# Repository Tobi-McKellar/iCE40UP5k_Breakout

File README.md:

This is a simple FPGA breakout board based on the iCE40UP5K. Exposing 16 GPIO via two 6x1 PMOD ports and one 6x2 PMOD port, as well as 11 LEDs, 3 buttons, and one capacitive touch button, the board can be powered via USB-C or the appropriate mounting holes. Programmed via [SOIC-Bite](https://github.com/SimonMerrett/SOICbite/blob/master/README.md). The schematic and PCB can be viewed online [here](https://kicanvas.org/?github=https%3A%2F%2Fgithub.com%2FTobi-McKellar%2FiCE40UP5k_Breakout%2Ftree%2Fmain%2FFPGA_SOM) via KiCanvas.

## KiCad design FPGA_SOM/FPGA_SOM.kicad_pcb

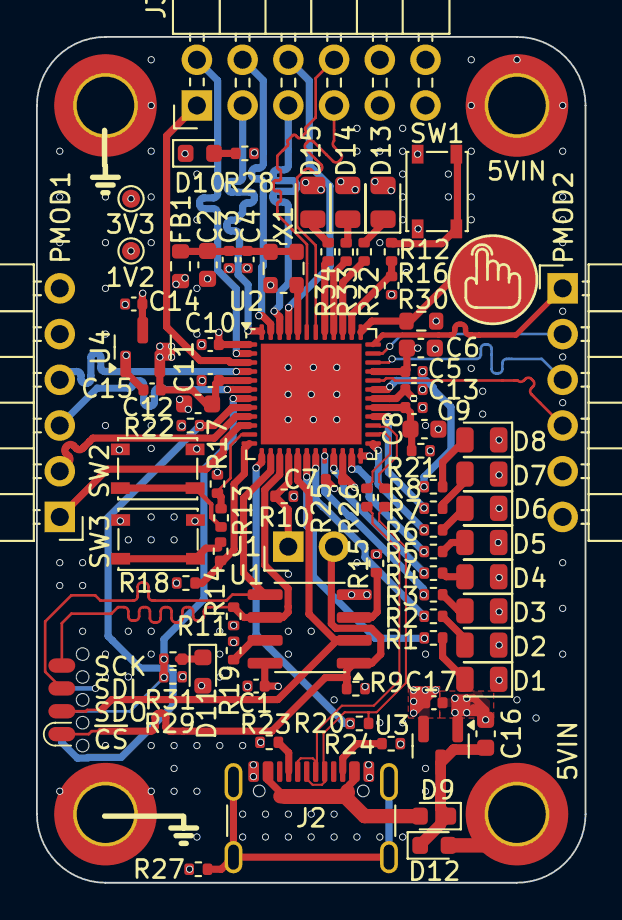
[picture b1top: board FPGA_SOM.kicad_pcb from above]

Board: 6 copper layers, 30.5 x 47.0 mm, 88 parts (0 on the bottom side), 73 nets.

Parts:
C1, C3, C5, C7, C9, C10, C11, C13: 100n; C_0402_1005Metric
C2, C16: 10u; C_0603_1608Metric
C4: 10n; C_0402_1005Metric
C6, C8, C12: 4.7u; C_0603_1608Metric
C14, C15, C17: 1u; C_0402_1005Metric
D1, D2, D14: GLED; LED_0805_2012Metric
D3, D4, D15: BLED; LED_0805_2012Metric
D5, D6: YLED; LED_0805_2012Metric
D7, D8, D13: RLED; LED_0805_2012Metric
D9, D12: D_Schottky; D_0603_1608Metric
D10, D11: LED; D_0603_1608Metric
FB1: FerriteBead; R_0603_1608Metric
H1, H2, H3, H4: MountingHole_Pad; MountingHole_3.2mm_M3_ISO7380_Pad_TopBottom
J1: Conn_01x02; PinHeader_1x02_P2.54mm_Vertical
J2: USB_C_Receptacle_USB2.0; USB_C_Receptacle_GCT_USB4105-xx-A_16P_TopMnt_Horizontal
J3: Conn_02x06_Top_Bottom; PinHeader_2x06_P2.54mm_Horizontal
J4: Conn_02x04_Counter_Clockwise; SOIC_clipProgSmall
J5, J6: Conn_01x06; PinHeader_1x06_P2.54mm_Horizontal
R1, R2, R3, R4, R5, R6: 470; R_0402_1005Metric
R7, R8, R12, R13, R14: 1k; R_0402_1005Metric
R9, R10, R11, R15, R16, R17, R18, R19, R22: 10k; R_0402_1005Metric
R20: 1k5; R_0402_1005Metric
R21: 100; R_0402_1005Metric
R23, R24: 5k1; R_0402_1005Metric
R25, R26: 22; R_0402_1005Metric
R27: 0; R_0402_1005Metric
R28, R31, R32, R33, R34: 2k2; R_0402_1005Metric
R29: 4k7; R_0402_1005Metric
R30: 1M; R_0603_1608Metric
SW1, SW2, SW3: SW_Push; SW_SPST_PTS810
TP1: 3V3; TestPoint_Pad_D1.0mm
TP2: 1V2; TestPoint_Pad_D1.0mm
U1: W25Q128JVSIQ; SOIC-8_3.9x4.9mm_P1.27mm
U2: ICE40UP5K-SG48ITR; QFN-48-1EP_7x7mm_P0.5mm_EP5.6x5.6mm
U3: AP2127N-3.3; SOT-23
U4: AP2127N-1.2; SOT-23
U5: Capacitive_touchpad
X1: SX2M36.000B10F20TNN; Oscillator_SMD_ECS_2520MV-xxx-xx-4Pin_2.5x2.0mm

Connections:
+5V: C16.2, D9.1 (K), D12.1 (K), U3.3 (VI)
/1V2: C11.1, C12.1, C13.1, C15.1, R21.2, TP2.1, U2.5 (VCC), U2.30 (VCC), U4.2 (VO)
/3V3: C1.1, C5.1, C6.1, C7.1, C10.1, C14.2, C17.1, D11.2 (A), D13.2 (A), D14.2 (A), D15.2 (A), FB1.1, J3.11, J3.12, J5.6, J6.6, R9.1, R10.1, R11.1, R15.1, R19.1, R22.1, R28.1, R29.1, R30.1, SW1.1, SW2.1, SW3.1, TP1.1, U1.8 (VCC), U2.1 (VCCIO_2), U2.22 (SPI_VCCIO1), U2.24 (VPP_2V5), U2.33 (VCCIO_0), U3.2 (VO), U4.3 (VI)
/31_button: R12.1, R16.2, U2.38 (IOT_50b)
/BLED0: R3.2, U2.20 (IOB_25b_G3)
/BLED1: R4.2, U2.21 (IOB_23b)
/Button_2: R13.1, R17.2, U2.11 (IOB_20a)
/Button_6: R14.1, R18.2, U2.12 (IOB_22a)
/CDONE: J4.7, R29.2, R31.1, U2.7 (CDONE)
/CLK_IN_G6: U2.44 (IOB_3b_G6), X1.3 (OUT)
/CRESET: J4.8, R22.2, U2.8 (~CRESET)
/Cap_touch: R30.2, U2.37 (IOT_45a_G1), U5.1 (Sense)
/D_N: R25.2, U2.26 (IOT_39a)
/D_P: R26.2, U2.27 (IOT_38b)
/Din_N: J2.A7 (D-), J2.B7 (D-), R25.1
/Din_P: J2.A6 (D+), J2.B6 (D+), R20.1, R26.1
/FLASH_DI: J4.3, U1.5 (DI(IO0)), U2.14 (IOB_32a_SPI_SO)
/FLASH_DO: J4.2, U1.2 (DO(IO1)), U2.17 (IOB_33b_SPI_SI)
/FLASH_SS: J1.2, J4.1, R9.2, U1.1 (~CS)
/GLED0: R1.2, U2.18 (IOB_31b)
/GLED1: R2.2, U2.19 (IOB_29b)
/ICE_SS: J1.1, R10.2, U2.16 (IOB_35b_SPI_SS)
/PMOD1_25: J5.4, U2.4 (IOB_8a)
/PMOD1_26: J5.2, U2.9 (IOB_16a)
/PMOD1_27: J5.3, U2.6 (IOB_13b)
/PMOD1_28: J5.1, U2.10 (IOB_18a)
/PMOD2_45: J3.4, U2.47 (IOB_2a)
/PMOD2_46: J3.3, U2.48 (IOB_4a)
/PMOD2_47: J3.2, U2.2 (IOB_6a)
/PMOD2_48: J3.1, U2.3 (IOB_9b)
/PMOD3_32: J6.4, U2.32 (IOT_43a)
/PMOD3_34: J6.3, U2.34 (IOT_44b)
/PMOD3_35_G0: J6.2, U2.35 (IOT_46b_G0)
/PMOD3_36: J6.1, U2.36 (IOT_48b)
/PMOD3_37_G1: J3.8, U2.43 (IOT_49a)
/PMOD3_38: J3.7, U2.42 (IOT_51a)
/PMOD3_42: J3.6, U2.45 (IOB_5b)
/PMOD3_43: J3.5, U2.46 (IOB_0a)
/RGB0: R32.1, U2.39 (RGB0)
/RGB1: R33.1, U2.40 (RGB1)
/RGB2: R34.1, U2.41 (RGB2)
/RLED0: R7.2, U2.28 (IOT_41a)
/RLED1: R8.2, U2.31 (IOT_42b)
/SCK: J4.4, R11.2, U1.6 (SCK), U2.15 (IOB_34a_SPI_SCK)
/USB_Detect: R20.2, U2.13 (IOB_24a)
/VCCPLL: C8.1, C9.1, R21.1, U2.29 (VCCPLL)
/V_OSC: C2.1, C3.1, C4.2, FB1.2, X1.1 (Tri-State), X1.4 (VDD)
/YLED0: R5.2, U2.23 (IOT_37a)
/YLED1: R6.2, U2.25 (IOT_36b)
GND: C1.2, C2.2, C3.2, C4.1, C5.2, C6.2, C7.2, C8.2, C9.2, C10.2, C11.2, C12.2, C13.2, C14.1, C15.2, C16.1, C17.2, D1.1 (K), D2.1 (K), D3.1 (K), D4.1 (K), D5.1 (K), D6.1 (K), D7.1 (K), D8.1 (K), D10.1 (K), H3.1, H4.1, J2.A1 (GND), J2.A12 (GND), J2.B1 (GND), J2.B12 (GND), J3.9, J3.10, J4.6, J5.5, J6.5, R16.1, R17.1, R18.1, R23.2, R24.2, R27.2, U1.4 (GND), U2.49 (GND), U3.1 (GND), U4.1 (GND), X1.2 (GND)
unnamed: D1.2 (A), R1.1
unnamed: D2.2 (A), R2.1
unnamed: D3.2 (A), R3.1
unnamed: D4.2 (A), R4.1
unnamed: D5.2 (A), R5.1
unnamed: D6.2 (A), R6.1
unnamed: D7.2 (A), R7.1
unnamed: D8.2 (A), R8.1
unnamed: D9.2 (A), J2.A4 (VBUS), J2.A9 (VBUS), J2.B4 (VBUS), J2.B9 (VBUS)
unnamed: D10.2 (A), R28.2
unnamed: D11.1 (K), R31.2
unnamed: D12.2 (A), H1.1, H2.1
unnamed: D13.1 (K), R32.2
unnamed: D14.1 (K), R33.2
unnamed: D15.1 (K), R34.2
unnamed: J2.A5 (CC1), R23.1
unnamed: J2.B5 (CC2), R24.1
unnamed: J2.S1 (SHIELD), R27.1
unnamed: R12.2, SW1.2
unnamed: R13.2, SW2.2
unnamed: R14.2, SW3.2
unnamed: R19.2, U1.7 (~HOLD)
unnamed: R15.2, U1.3 (~WP)

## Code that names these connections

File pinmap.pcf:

# Clock
set_io clk 44
set_frequency clk 24.0

# Normal LEDs
set_io -nowarn YLED0 23
set_io -nowarn YLED1 25
set_io -nowarn RLED0 28
set_io -nowarn RLED1 31
set_io -nowarn GLED0 18
set_io -nowarn GLED1 19
set_io -nowarn BLED0 20
set_io -nowarn BLED1 21

# RGB LEDs
set_io -nowarn RGB_R 39
set_io -nowarn RGB_G 40
set_io -nowarn RGB_B 41

# Pushbuttons
set_io -nowarn pattern[0] 38
set_io -nowarn pattern[1] 11
set_io -nowarn pattern[2] 12

# Capacitive touch button
set_io -nowarn pattern[3] 37

# PMODs

# 3V3 GND 3 2 1 0
# 3V3 GND 7 6 5 4

# PMOD1
set_io -nowarn PMOD1_3 4
set_io -nowarn PMOD1_2 6
set_io -nowarn PMOD1_1 9
set_io -nowarn PMOD1_0 10

# PMOD2
set_io -nowarn PMOD2_3 32
set_io -nowarn PMOD2_2 34
set_io -nowarn PMOD2_1 35
set_io -nowarn PMOD2_0 36

# PMOD3
set_io -nowarn PMOD3_7 43
set_io -nowarn PMOD3_6 45
set_io -nowarn PMOD3_5 47
set_io -nowarn PMOD3_4 2
set_io -nowarn PMOD3_3 42
set_io -nowarn PMOD3_2 46
set_io -nowarn PMOD3_1 48
set_io -nowarn PMOD3_0 3

# USB
set_io -nowarn USB_DP 27
set_io -nowarn USB_DN 26
set_io -nowarn USB_PULLUP 13

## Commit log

2024-04-17 First commit.
2024-05-04 Version one. Had some errors documented in schematic which I will fix in version 2.
2024-05-04 First attempt at V2. Likely to be changed in the near future.
2024-05-04 Added JLC text and my name. to silkscreen.
2024-05-06 add pullup resistor to sck on schematic.
2024-05-15 Saving progress.
2024-05-17 Remove some unnecessary capacitors and resize others.
2024-05-17 Add png of schematic for V2.
2024-05-18 Added silkscreen and removed unneded test points.
2024-05-18 ficing small things and adding qr code to repo.
2024-05-18 Added button and clarified silkscreen for RGB leds.
2024-05-31 Added silkscreen, stitching vias, and quality of life improvements.
2024-06-12 QOL changes before production.
2024-06-12 Added notes to schematic.
2024-06-12 Add new schematic.
2024-06-12 Rename Screen Shot 2024-06-13 at 12.31.32 AM.png to schematic.png
2024-06-23 Ignore more autosaves and lock files.
2024-06-23 Added ethernet, usb-c, capacitive touch button, and PMOD to schematic. Started PCB layout for V3.
2024-12-23 V3. New form factor, many improvements.
2024-12-28 Final version 3 sent for assembly.
2025-01-27 Create pinmap.pcf
    Add pinmap file.
2025-01-27 Update README.md
    Add some whitespace for readability.
2025-05-22 Kicad Update changes some things. Also reorganise nets.
